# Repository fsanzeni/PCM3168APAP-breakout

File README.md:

# PCM3168APAP Breakout Board

A breakout board for the Texas Instruments PCM3168APAP audio codec, featuring 6 analog inputs and 8 analog outputs with high-quality buffering and filtering circuitry.
| PCB Front | PCB Back |
|-----------|----------|
|  |  |

## Overview

This evaluation board is based on the [TI TIDA-00609](https://www.ti.com/tool/TIDA-00609) reference design and provides a complete interface to the [PCM3168APAP](https://www.ti.com/product/PCM3168A/part-details/PCM3168APAP) - a 24-bit, 96kHz/192kHz, 6-in/8-out audio codec. The board includes analog input buffering with anti-aliasing filters, differential-to-single-ended output conversion, and integrated power regulation (via LDOs for 5v and 3.3v).

## Features

### Audio Codec
- **ADC**: 6-channel, 24-bit delta-sigma ADC with 107 dB dynamic range (differential), 104 dB (single-ended)
- **DAC**: 8-channel, 24-bit delta-sigma DAC with 112 dB dynamic range and differential 8V peak-to-peak outputs
- Sampling rates: 8 kHz to 192 kHz (ADC up to 96 kHz, DAC up to 192 kHz)
- Supports I²S, left-justified, right-justified, DSP, and TDM audio formats

### Analog Signal Path

#### Inputs (6 channels)
- 3.5mm TRS jack connectors for each stereo input pair
- Buffer and anti-aliasing low-pass filter based on [OPA4134](https://www.ti.com/product/OPA4134)/[OPA2134](https://www.ti.com/product/OPA2134) op-amps
- Configured for 2V RMS input, 0.5x gain, -3dB at 48 kHz 
- Output: 1V RMS to ADC
- Common-mode reference voltage (VCOMAD) generation

#### Outputs (8 channels)
- Two 6-pin headers providing 4 channels each
- Post-LPF and differential-to-single-ended conversion using OPA4134 op-amps
- Configured for 4V peak-to-peak DAC output, 0.747x gain, -3dB at 53 kHz
- Output: 2V RMS single-ended

### Digital Interface
- **I²S/Audio** (6-pin header): MCLK, BCK_ADC, LRCK_ADC, BCK_DAC, LRCK_DAC, and ground
- **I²C** (4-pin header): SDA, SCL, 3.3V, and ground
- **Digital Input** (4-pin header): DIN2, DIN3, SDIN (DIN1), and ground
- **Digital Output** (4-pin header): DOUT1, DOUT2, DOUT3, and ground
- **Reset** (2-pin header): Active-low reset with buffer IC ([SN74LVC2G34](https://www.ti.com/product/SN74LVC2G34))

### Configuration
- I²C mode (MODE pin tied to GND)
- I²C device address: 0x88
- Test points for ZERO and OVERFLOW flags
- Status LEDs: Green (ZERO), Yellow (OVERFLOW)

### Power Supply
- Input voltage: 6.2V to 18V
- Dual linear regulators (AMS1117):
  - 5V output for analog circuitry
  - 3.3V output for digital logic
- Comprehensive decoupling throughout

## BOM Highlights

### Key Components
- **IC101**: PCM3168APAP (HTQFP-64 package)
- **IC102**: SN74LVC2G34DRLR (dual buffer for reset/LEDs)
- **U201-U202, U301-U302**: OPA4134UA/OPA2134 (audio op-amps)
- **U401-U402**: AMS1117-5.0 and AMS1117-3.3 (linear regulators)

### Connectors
- J101: 6-pin I²S header
- J102: 4-pin I²C header
- J103-J104: 4-pin DIN/DOUT headers
- J201-J203: 3.5mm TRS analog input jacks
- J301-J302: 6-pin analog output headers
- J401: 2-pin power input

## Usage Notes

- Ensure proper power supply voltage range (6.2V minimum to avoid dropout on regulators) 
- The board is configured for I²C control by default
- All analog inputs accept balanced TRS connections or can be used with unbalanced sources
- Output headers provide differential pairs that have been converted to single-ended signals 

## License

[MIT License](./LICENSE)

## Revision History

- **v0.1** (2026-01-13): Initial release

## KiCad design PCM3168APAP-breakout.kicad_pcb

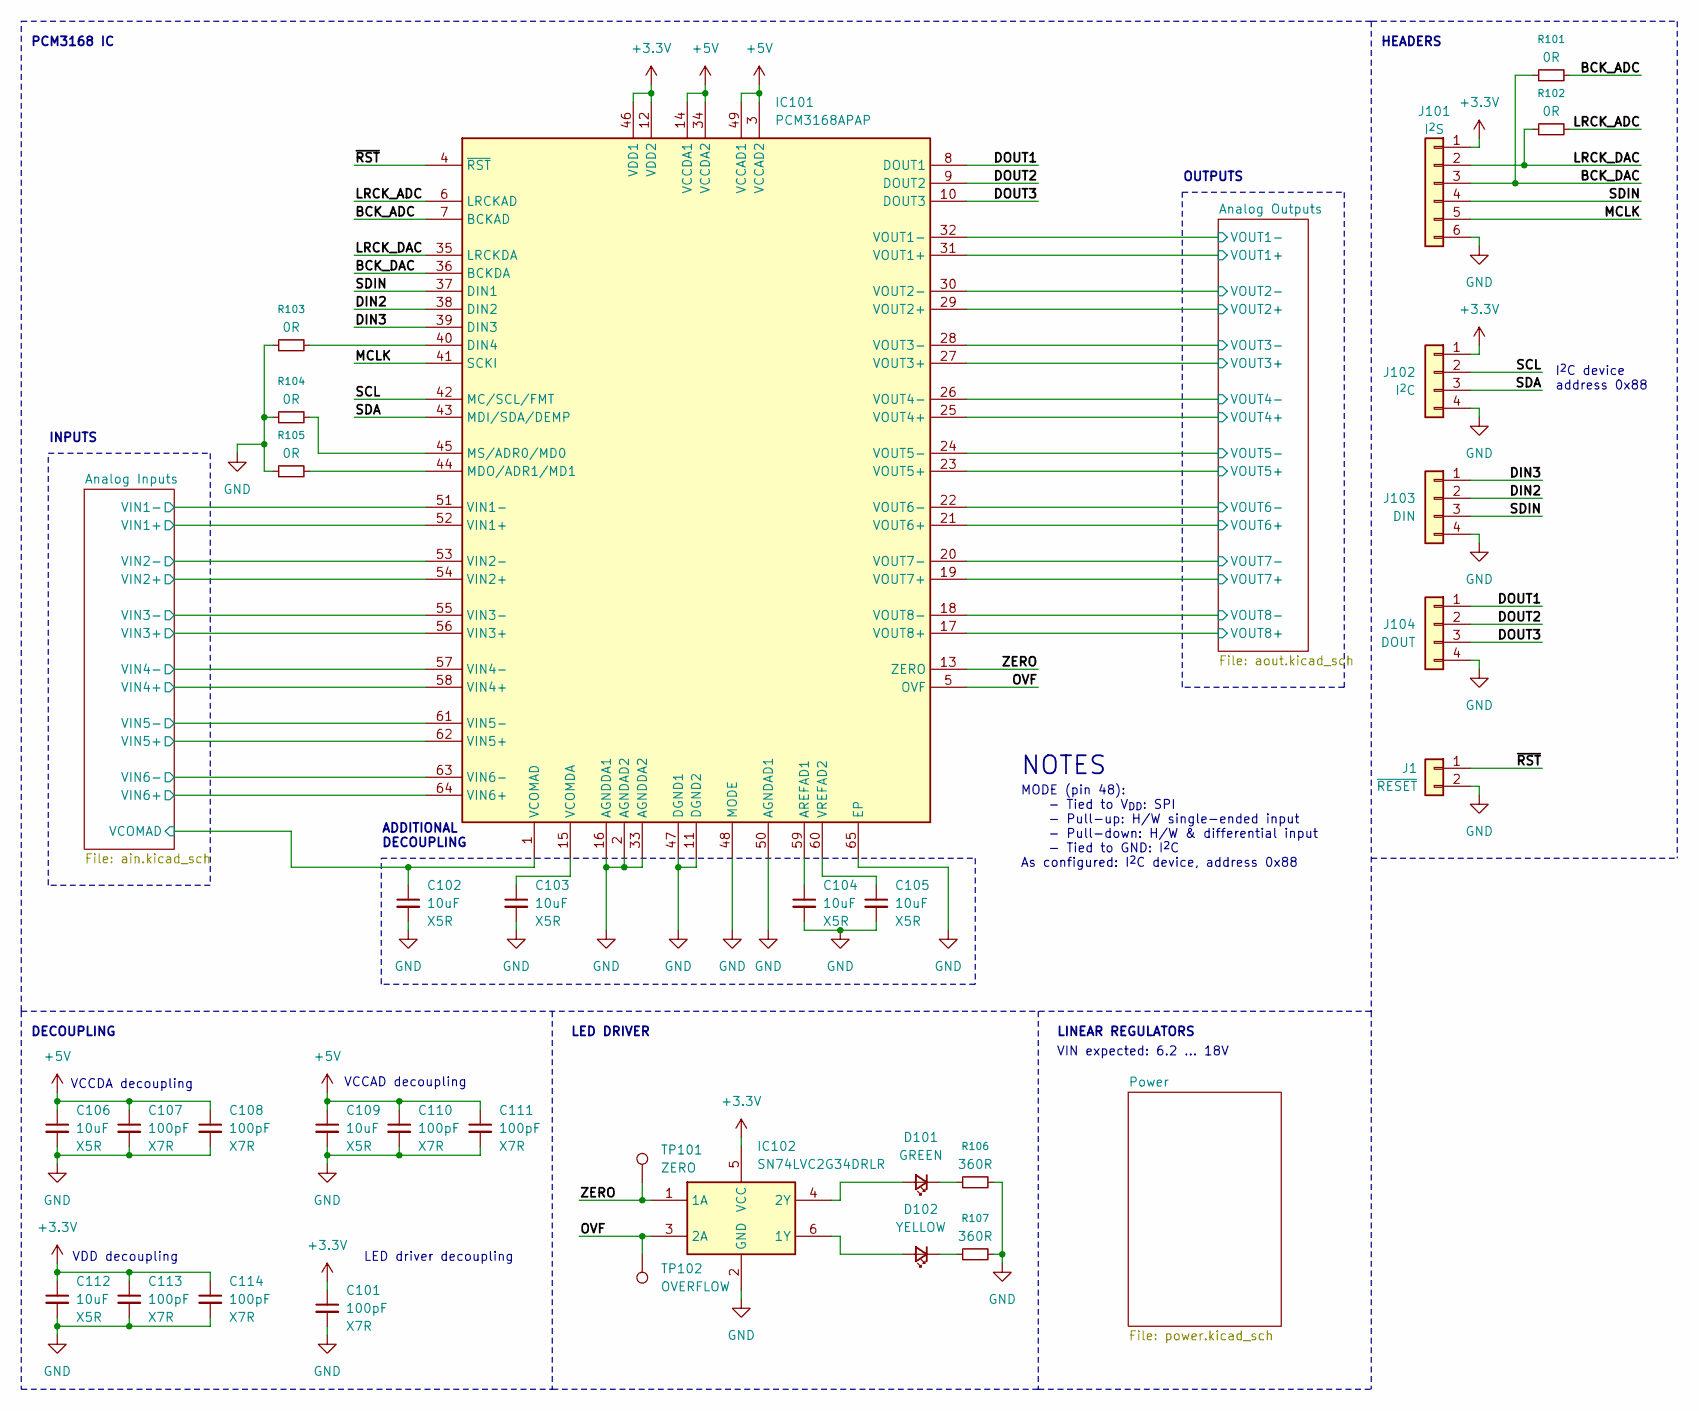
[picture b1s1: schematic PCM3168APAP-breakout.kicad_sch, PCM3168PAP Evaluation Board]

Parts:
C101, C107, C108, C110, C111, C113, C114: 100pF; C_0402_1005Metric
C102, C103, C104, C105, C106, C109, C112: 10uF; C_0603_1608Metric
D101: GREEN; LED_0603_1608Metric
D102: YELLOW; LED_0603_1608Metric
IC101: PCM3168APAP; QFP50P1200X1200X120-65N; Mouser Part Number 595-PCM3168APAP
IC102: SN74LVC2G34DRLR; SOTFL50P160X60-6N; Mouser Part Number 595-SN74LVC2G34DRLR
J1: ~{RESET}; PinHeader_1x02_P2.54mm_Vertical
J101: I^{2}S; PinHeader_1x06_P2.54mm_Vertical
J102: I^{2}C; PinHeader_1x04_P2.54mm_Vertical
J103: DIN; PinHeader_1x04_P2.54mm_Vertical
J104: DOUT; PinHeader_1x04_P2.54mm_Vertical
R101, R102, R103, R104, R105: 0R; R_0402_1005Metric
R106, R107: 360R; R_0402_1005Metric
TP101: ZERO; TestPoint_Pad_1.0x1.0mm
TP102: OVERFLOW; TestPoint_Pad_1.0x1.0mm

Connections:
+3.3V: C101.1, C112.1, C113.1, C114.1, IC101.12 (VDD2), IC101.46 (VDD1), IC102.5 (VCC), J101.1, J102.1; also elsewhere on the board
+5V: C106.1, C107.1, C108.1, C109.1, C110.1, C111.1, IC101.3 (VCCAD2), IC101.14 (VCCDA1), IC101.34 (VCCDA2), IC101.49 (VCCAD1); also elsewhere on the board
/Analog Inputs/VCOMAD: C102.1, IC101.1 (VCOMAD); also elsewhere on the board
/Analog Inputs/VIN1+: IC101.52 (VIN1+); also elsewhere on the board
/Analog Inputs/VIN1-: IC101.51 (VIN1-); also elsewhere on the board
/Analog Inputs/VIN2+: IC101.54 (VIN2+); also elsewhere on the board
/Analog Inputs/VIN2-: IC101.53 (VIN2-); also elsewhere on the board
/Analog Inputs/VIN3+: IC101.56 (VIN3+); also elsewhere on the board
/Analog Inputs/VIN3-: IC101.55 (VIN3-); also elsewhere on the board
/Analog Inputs/VIN4+: IC101.58 (VIN4+); also elsewhere on the board
/Analog Inputs/VIN4-: IC101.57 (VIN4-); also elsewhere on the board
/Analog Inputs/VIN5+: IC101.62 (VIN5+); also elsewhere on the board
/Analog Inputs/VIN5-: IC101.61 (VIN5-); also elsewhere on the board
/Analog Inputs/VIN6+: IC101.64 (VIN6+); also elsewhere on the board
/Analog Inputs/VIN6-: IC101.63 (VIN6-); also elsewhere on the board
/Analog Outputs/VOUT1+: IC101.31 (VOUT1+); also elsewhere on the board
/Analog Outputs/VOUT1-: IC101.32 (VOUT1-); also elsewhere on the board
/Analog Outputs/VOUT2+: IC101.29 (VOUT2+); also elsewhere on the board
/Analog Outputs/VOUT2-: IC101.30 (VOUT2-); also elsewhere on the board
/Analog Outputs/VOUT3+: IC101.27 (VOUT3+); also elsewhere on the board
/Analog Outputs/VOUT3-: IC101.28 (VOUT3-); also elsewhere on the board
/Analog Outputs/VOUT4+: IC101.25 (VOUT4+); also elsewhere on the board
/Analog Outputs/VOUT4-: IC101.26 (VOUT4-); also elsewhere on the board
/Analog Outputs/VOUT5+: IC101.23 (VOUT5+); also elsewhere on the board
/Analog Outputs/VOUT5-: IC101.24 (VOUT5-); also elsewhere on the board
/Analog Outputs/VOUT6+: IC101.21 (VOUT6+); also elsewhere on the board
/Analog Outputs/VOUT6-: IC101.22 (VOUT6-); also elsewhere on the board
/Analog Outputs/VOUT7+: IC101.19 (VOUT7+); also elsewhere on the board
/Analog Outputs/VOUT7-: IC101.20 (VOUT7-); also elsewhere on the board
/Analog Outputs/VOUT8+: IC101.17 (VOUT8+); also elsewhere on the board
/Analog Outputs/VOUT8-: IC101.18 (VOUT8-); also elsewhere on the board
/BCK_ADC: IC101.7 (BCKAD), R101.2
/BCK_DAC: IC101.36 (BCKDA), J101.3, R101.1
/DIN2: IC101.38 (DIN2), J103.2
/DIN3: IC101.39 (DIN3), J103.1
/DOUT1: IC101.8 (DOUT1), J104.1
/DOUT2: IC101.9 (DOUT2), J104.2
/DOUT3: IC101.10 (DOUT3), J104.3
/LRCK_ADC: IC101.6 (LRCKAD), R102.2
/LRCK_DAC: IC101.35 (LRCKDA), J101.2, R102.1
/MCLK: IC101.41 (SCKI), J101.5
/OVF: IC101.5 (OVF), IC102.3 (2A), TP102.1
/SCL: IC101.42 (MC/SCL/FMT), J102.2
/SDA: IC101.43 (MDI/SDA/DEMP), J102.3
/SDIN: IC101.37 (DIN1), J101.4, J103.3
/ZERO: IC101.13 (ZERO), IC102.1 (1A), TP101.1
/~RST: IC101.4 (~RST), J1.1
GND: C101.2, C102.2, C103.2, C104.2, C105.2, C106.2, C107.2, C108.2, C109.2, C110.2, C111.2, C112.2, C113.2, C114.2, IC101.2 (AGNDAD2), IC101.11 (DGND2), IC101.16 (AGNDDA1), IC101.33 (AGNDDA2), IC101.47 (DGND1), IC101.48 (MODE), IC101.50 (AGNDAD1), IC101.65 (EP), IC102.2 (GND), J1.2, J101.6, J102.4, J103.4, J104.4, R103.1, R104.1, R105.1, R106.2, R107.2; also elsewhere on the board
unnamed: D101.2 (A), IC102.4 (2Y)
unnamed: D101.1 (K), R106.1
unnamed: D102.2 (A), IC102.6 (1Y)
unnamed: D102.1 (K), R107.1
unnamed: C104.1, IC101.59 (AREFAD1)
unnamed: IC101.40 (DIN4), R103.2
unnamed: IC101.44 (MDO/ADR1/MD1), R105.2
unnamed: IC101.45 (MS/ADR0/MD0), R104.2
unnamed: C103.1, IC101.15 (VCOMDA)
unnamed: C105.1, IC101.60 (VREFAD2)

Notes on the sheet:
LED DRIVER
I^{2}C device address 0x88
DECOUPLING
PCM3168 IC
VCCAD decoupling
ADDITIONAL DECOUPLING
OUTPUTS
VDD decoupling
VCCDA decoupling
VIN expected: 6.2 ... 18V
LED driver decoupling
INPUTS
MODE (pin 48): - Tied to V_{DD}: SPI - Pull-up: H/W single-ended input - Pull-down: H/W & differential input - Tied to GND: I^{2}C As configured: I^{2}C device, address 0x88
NOTES
HEADERS
LINEAR REGULATORS

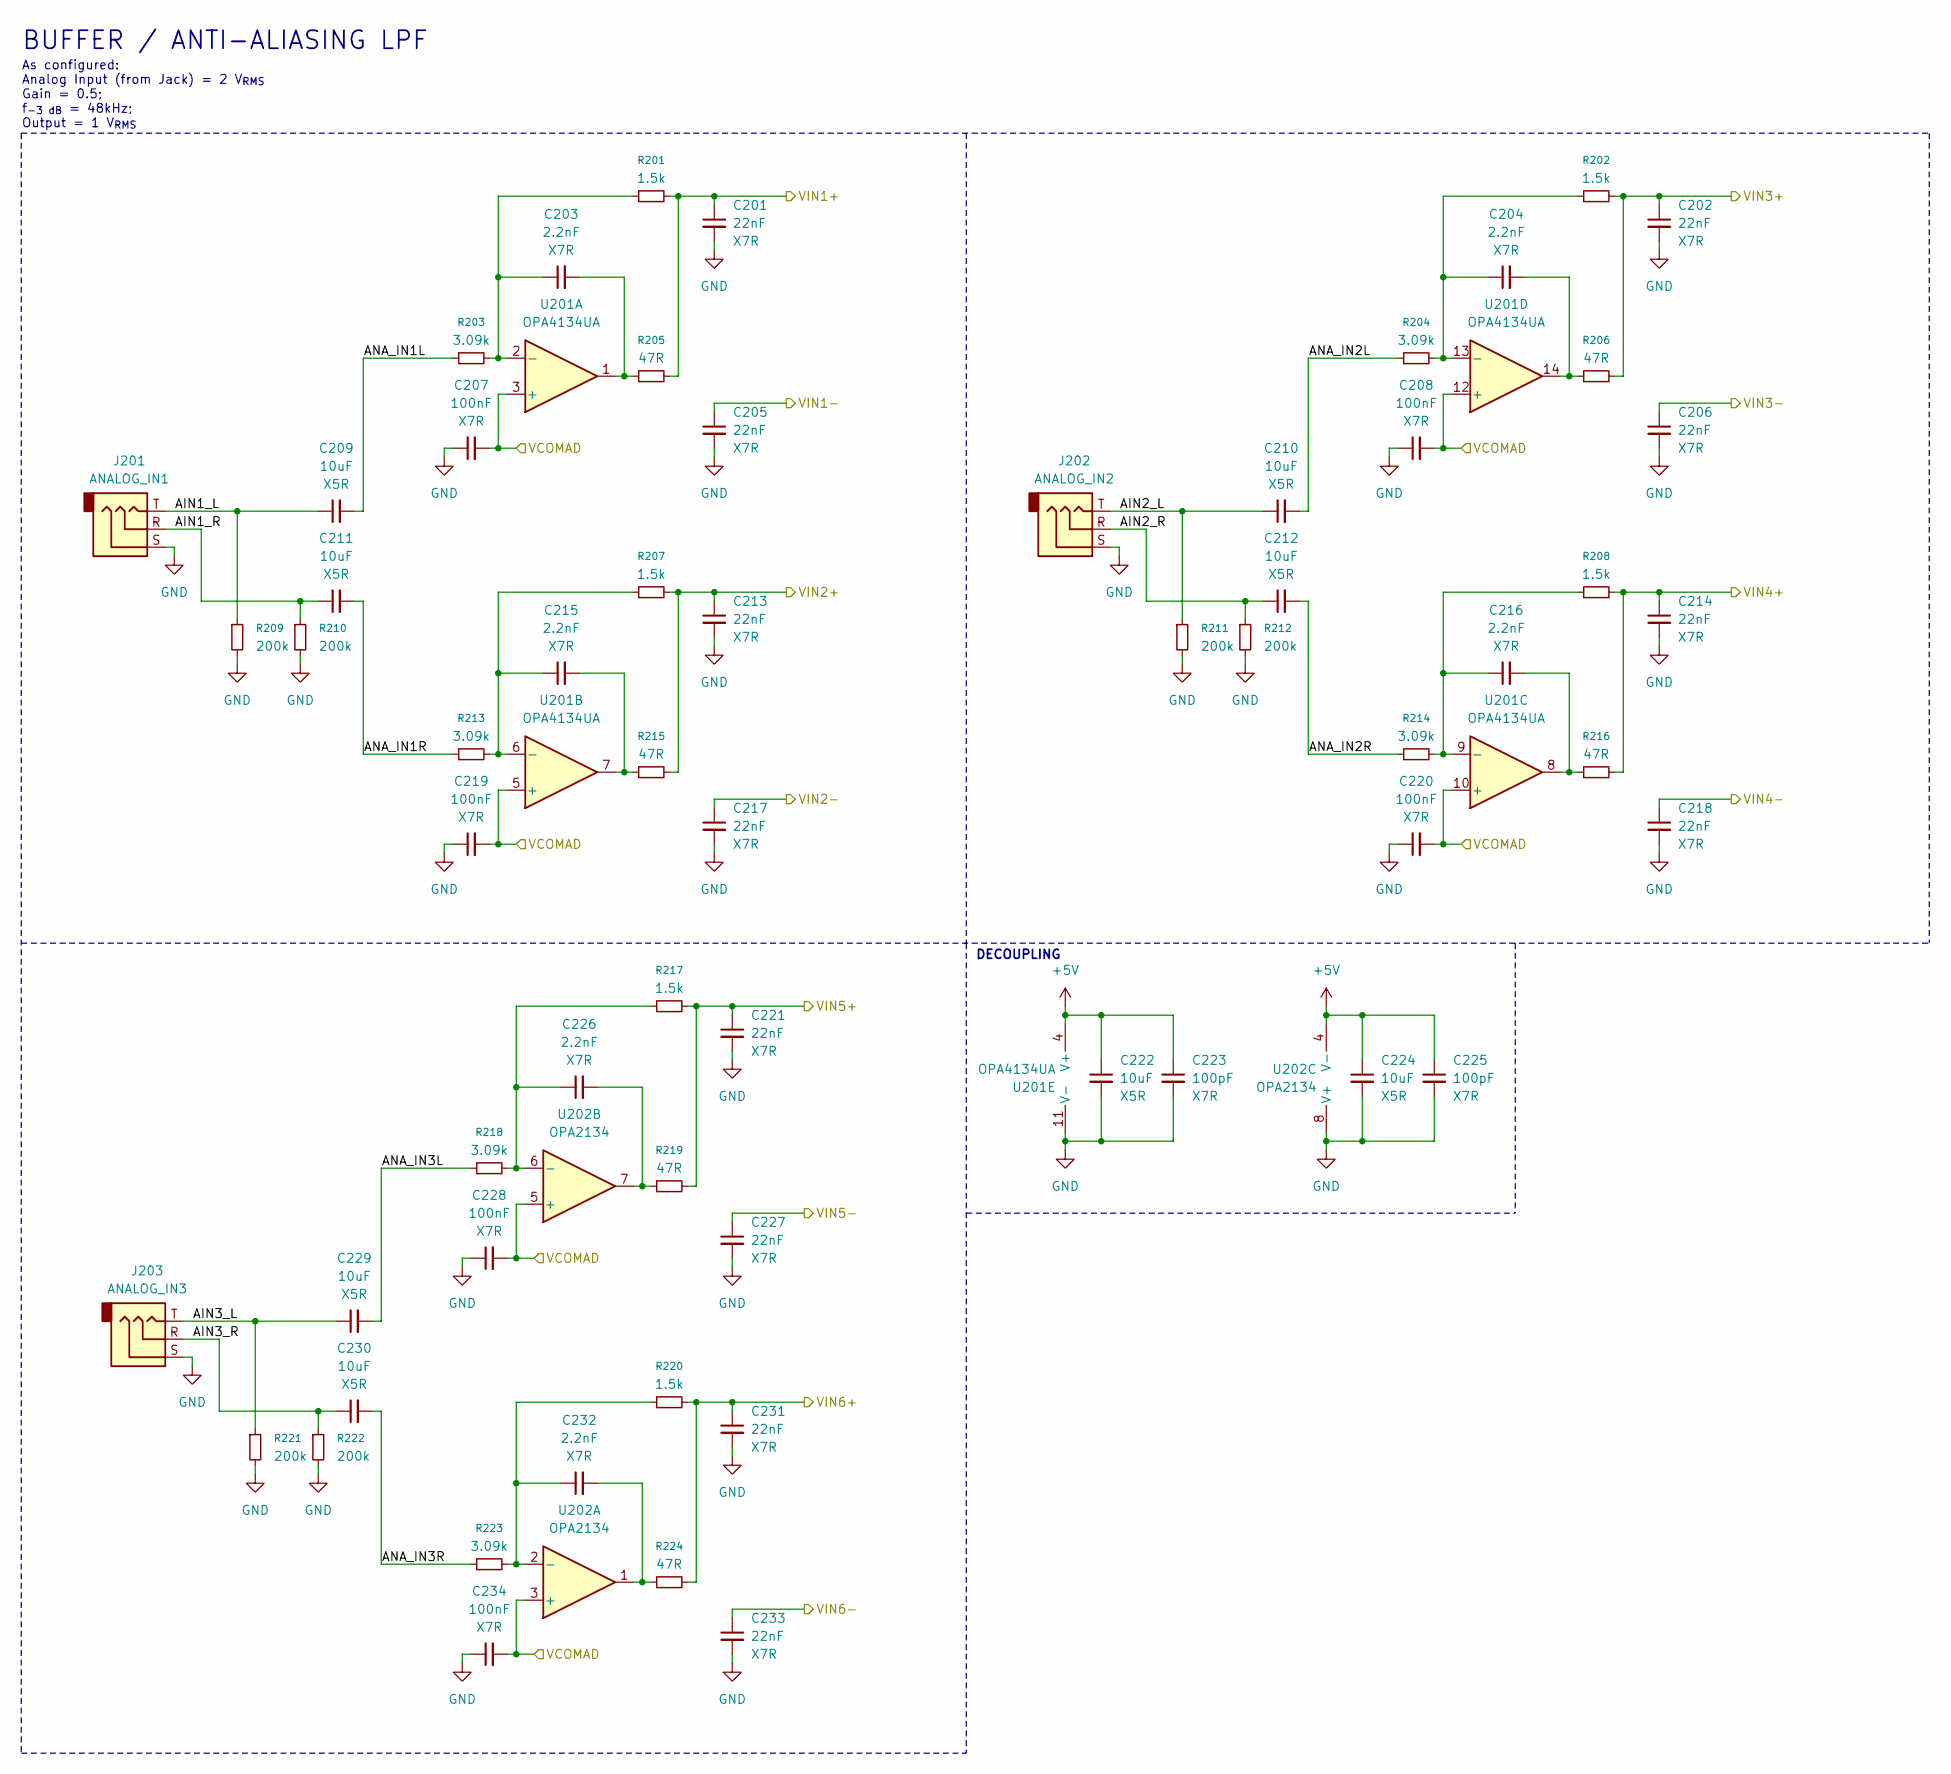
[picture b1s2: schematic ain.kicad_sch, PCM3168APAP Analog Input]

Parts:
C201, C202, C205, C206, C213, C214, C217, C218, C221, C227, C231, C233: 22nF; C_0402_1005Metric
C203, C204, C215, C216, C226, C232: 2.2nF; C_0402_1005Metric
C207, C208, C219, C220, C228, C234: 100nF; C_0402_1005Metric
C209, C210, C211, C212, C222, C224, C229, C230: 10uF; C_0603_1608Metric
C223, C225: 100pF; C_0402_1005Metric
J201: ANALOG_IN1; SJ335083ATR
J202: ANALOG_IN2; SJ335083ATR
J203: ANALOG_IN3; SJ335083ATR
R201, R202, R207, R208, R217, R220: 1.5k; R_0402_1005Metric
R203, R204, R213, R214, R218, R223: 3.09k; R_0402_1005Metric
R205, R206, R215, R216, R219, R224: 47R; R_0402_1005Metric
R209, R210, R211, R212, R221, R222: 200k; R_0402_1005Metric
U201: OPA4134UA; SOIC-14_3.9x8.7mm_P1.27mm
U202: OPA2134; SOIC-8_3.9x4.9mm_P1.27mm

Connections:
+5V: C222.1, C223.1, C224.1, C225.1, U201.4 (V+), U202.4 (V-); also elsewhere on the board
/Analog Inputs/AIN1_L: C209.1, J201.T, R209.1
/Analog Inputs/AIN1_R: C211.1, J201.R, R210.1
/Analog Inputs/AIN2_L: C210.1, J202.T, R211.1
/Analog Inputs/AIN2_R: C212.1, J202.R, R212.1
/Analog Inputs/AIN3_L: C229.1, J203.T, R221.1
/Analog Inputs/AIN3_R: C230.1, J203.R, R222.1
/Analog Inputs/ANA_IN1L: C209.2, R203.1
/Analog Inputs/ANA_IN1R: C211.2, R213.1
/Analog Inputs/ANA_IN2L: C210.2, R204.1
/Analog Inputs/ANA_IN2R: C212.2, R214.1
/Analog Inputs/ANA_IN3L: C229.2, R218.1
/Analog Inputs/ANA_IN3R: C230.2, R223.1
/Analog Inputs/VCOMAD: C207.2, C208.2, C219.2, C220.2, C228.2, C234.2, U201.3 (+), U201.5 (+), U201.10 (+), U201.12 (+), U202.3 (+), U202.5 (+); also elsewhere on the board
/Analog Inputs/VIN1+: C201.1, R201.2, R205.2; also elsewhere on the board
/Analog Inputs/VIN1-: C205.1; also elsewhere on the board
/Analog Inputs/VIN2+: C213.1, R207.2, R215.2; also elsewhere on the board
/Analog Inputs/VIN2-: C217.1; also elsewhere on the board
/Analog Inputs/VIN3+: C202.1, R202.2, R206.2; also elsewhere on the board
/Analog Inputs/VIN3-: C206.1; also elsewhere on the board
/Analog Inputs/VIN4+: C214.1, R208.2, R216.2; also elsewhere on the board
/Analog Inputs/VIN4-: C218.1; also elsewhere on the board
/Analog Inputs/VIN5+: C221.1, R217.2, R219.2; also elsewhere on the board
/Analog Inputs/VIN5-: C227.1; also elsewhere on the board
/Analog Inputs/VIN6+: C231.1, R220.2, R224.2; also elsewhere on the board
/Analog Inputs/VIN6-: C233.1; also elsewhere on the board
GND: C201.2, C202.2, C205.2, C206.2, C207.1, C208.1, C213.2, C214.2, C217.2, C218.2, C219.1, C220.1, C221.2, C222.2, C223.2, C224.2, C225.2, C227.2, C228.1, C231.2, C233.2, C234.1, J201.S, J202.S, J203.S, R209.2, R210.2, R211.2, R212.2, R221.2, R222.2, U201.11 (V-), U202.8 (V+); also elsewhere on the board
unnamed: C203.2, R205.1, U201.1
unnamed: C204.2, R206.1, U201.14
unnamed: C215.2, R215.1, U201.7
unnamed: C216.2, R216.1, U201.8
unnamed: C226.2, R219.1, U202.7
unnamed: C232.2, R224.1, U202.1
unnamed: C203.1, R201.1, R203.2, U201.2 (-)
unnamed: C215.1, R207.1, R213.2, U201.6 (-)
unnamed: C216.1, R208.1, R214.2, U201.9 (-)
unnamed: C204.1, R202.1, R204.2, U201.13 (-)
unnamed: C232.1, R220.1, R223.2, U202.2 (-)
unnamed: C226.1, R217.1, R218.2, U202.6 (-)

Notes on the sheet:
DECOUPLING
BUFFER / ANTI-ALIASING LPF
As configured: Analog Input (from Jack) = 2 V_{RMS} Gain = 0.5; f_{-3 dB} = 48kHz; Output = 1 V_{RMS}

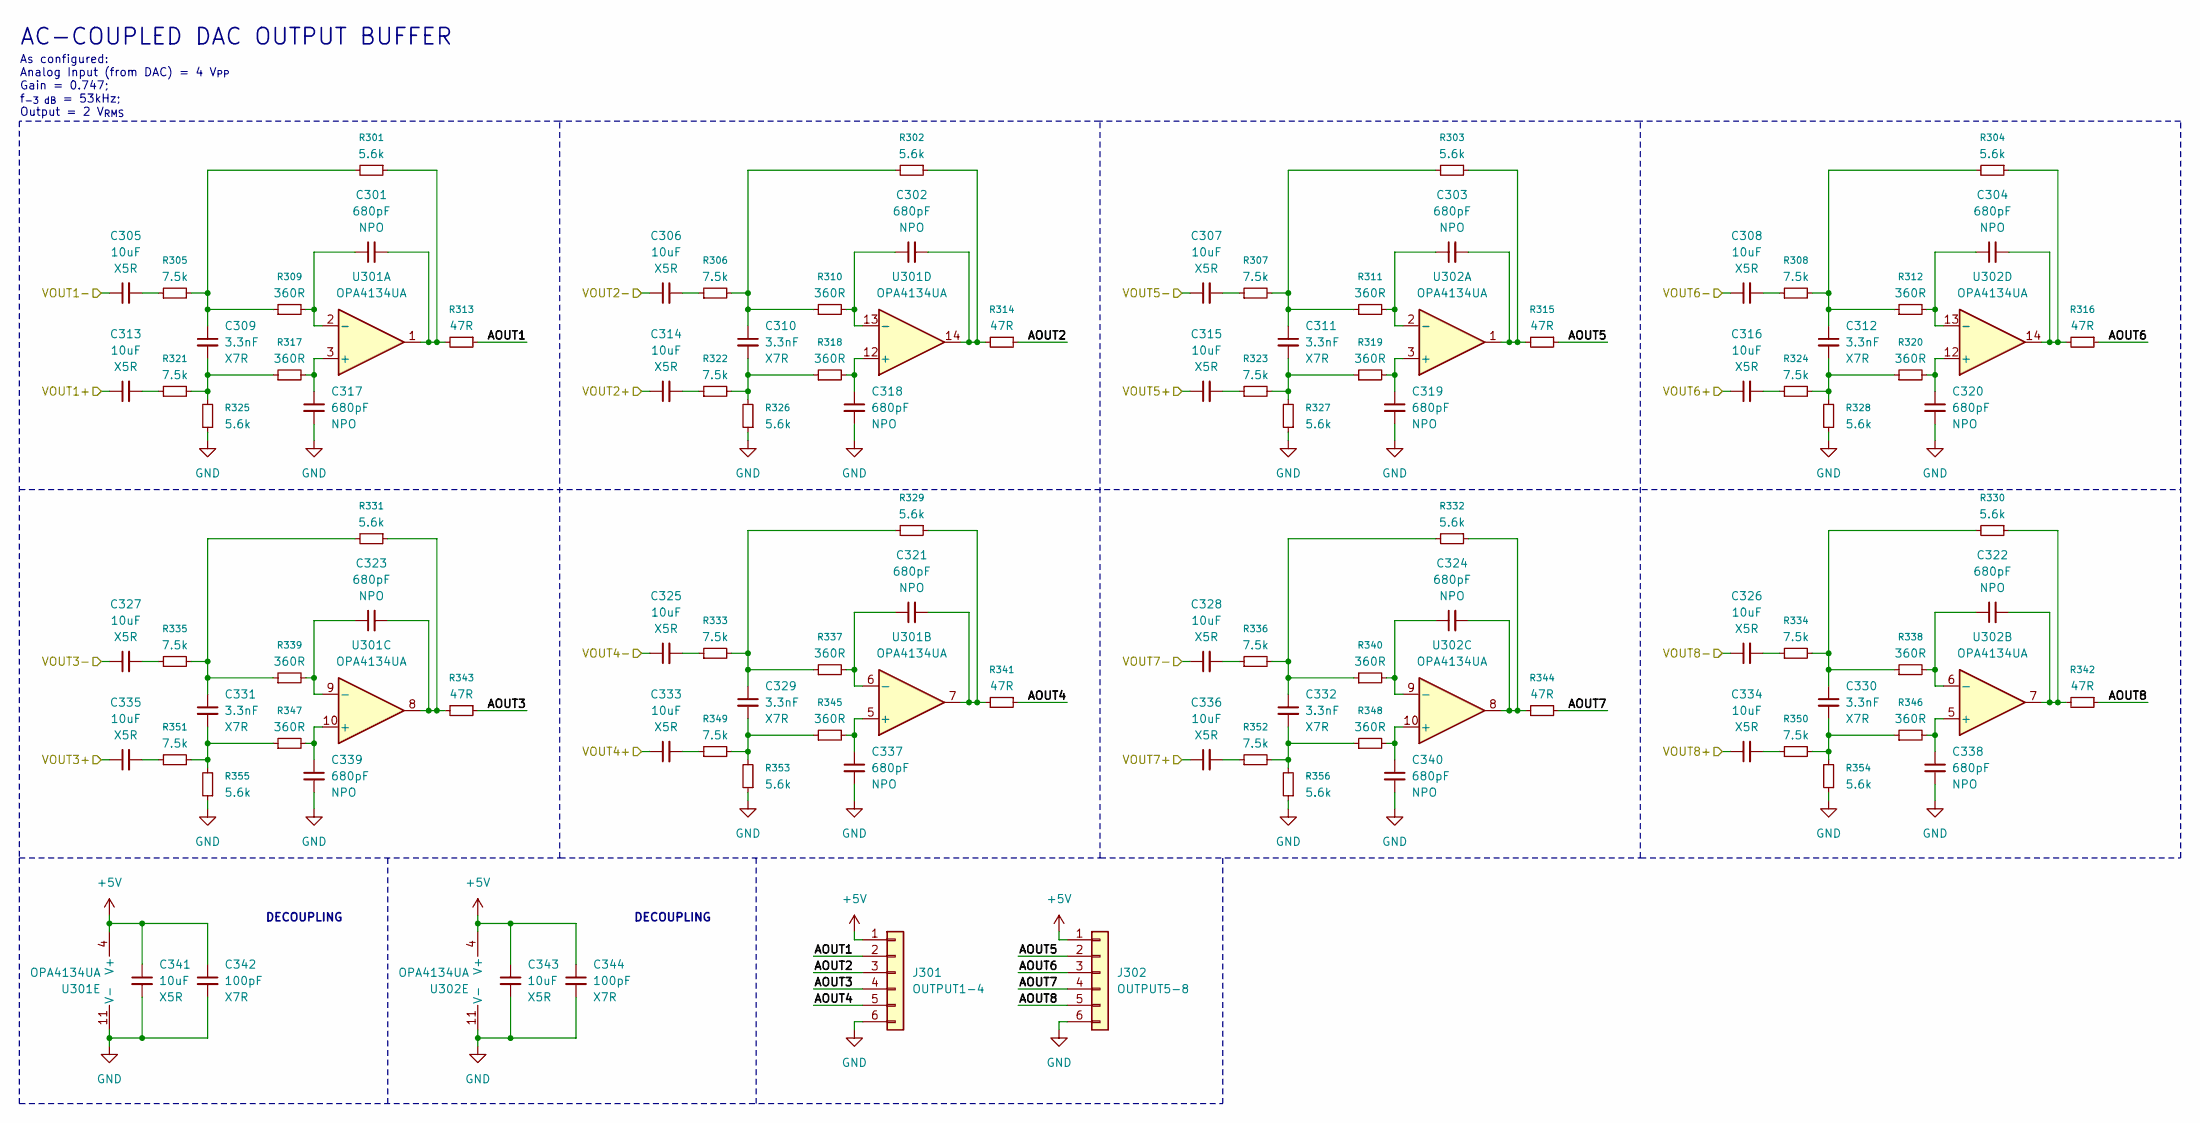
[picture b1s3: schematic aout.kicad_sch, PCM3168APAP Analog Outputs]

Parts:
C301, C302, C303, C304, C321, C322, C323, C324: 680pF; C_0603_1608Metric
C305, C306, C307, C308, C313, C314, C315, C316, C325, C326, C327, C328, C333, C334, C335, C336, C341, C343: 10uF; C_0603_1608Metric
C309, C310, C311, C312, C329, C330, C331, C332: 3.3nF; C_0402_1005Metric
C317, C318, C319, C320, C337, C338, C339, C340: 680pF; C_0402_1005Metric
C342, C344: 100pF; C_0402_1005Metric
J301: OUTPUT1-4; PinHeader_1x06_P2.54mm_Vertical
J302: OUTPUT5-8; PinHeader_1x06_P2.54mm_Vertical
R301, R302, R303, R304, R325, R326, R327, R328, R329, R330, R331, R332, R353, R354, R355, R356: 5.6k; R_0402_1005Metric
R305, R306, R307, R308, R321, R322, R323, R324, R333, R334, R335, R336, R349, R350, R351, R352: 7.5k; R_0402_1005Metric
R309, R310, R311, R312, R317, R318, R319, R320, R337, R338, R339, R340, R345, R346, R347, R348: 360R; R_0402_1005Metric
R313, R314, R315, R316, R341, R342, R343, R344: 47R; R_0402_1005Metric
U301, U302: OPA4134UA; SOIC-14_3.9x8.7mm_P1.27mm

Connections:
+5V: C341.1, C342.1, C343.1, C344.1, J301.1, J302.1, U301.4 (V+), U302.4 (V+); also elsewhere on the board
/Analog Outputs/AOUT1: J301.2, R313.1
/Analog Outputs/AOUT2: J301.3, R314.1
/Analog Outputs/AOUT3: J301.4, R343.1
/Analog Outputs/AOUT4: J301.5, R341.1
/Analog Outputs/AOUT5: J302.2, R315.1
/Analog Outputs/AOUT6: J302.3, R316.1
/Analog Outputs/AOUT7: J302.4, R344.1
/Analog Outputs/AOUT8: J302.5, R342.1
/Analog Outputs/VOUT1+: C313.1; also elsewhere on the board
/Analog Outputs/VOUT1-: C305.1; also elsewhere on the board
/Analog Outputs/VOUT2+: C314.1; also elsewhere on the board
/Analog Outputs/VOUT2-: C306.1; also elsewhere on the board
/Analog Outputs/VOUT3+: C335.1; also elsewhere on the board
/Analog Outputs/VOUT3-: C327.1; also elsewhere on the board
/Analog Outputs/VOUT4+: C333.1; also elsewhere on the board
/Analog Outputs/VOUT4-: C325.1; also elsewhere on the board
/Analog Outputs/VOUT5+: C315.1; also elsewhere on the board
/Analog Outputs/VOUT5-: C307.1; also elsewhere on the board
/Analog Outputs/VOUT6+: C316.1; also elsewhere on the board
/Analog Outputs/VOUT6-: C308.1; also elsewhere on the board
/Analog Outputs/VOUT7+: C336.1; also elsewhere on the board
/Analog Outputs/VOUT7-: C328.1; also elsewhere on the board
/Analog Outputs/VOUT8+: C334.1; also elsewhere on the board
/Analog Outputs/VOUT8-: C326.1; also elsewhere on the board
GND: C317.2, C318.2, C319.2, C320.2, C337.2, C338.2, C339.2, C340.2, C341.2, C342.2, C343.2, C344.2, J301.6, J302.6, R325.1, R326.1, R327.1, R328.1, R353.1, R354.1, R355.1, R356.1, U301.11 (V-), U302.11 (V-); also elsewhere on the board
unnamed: C301.2, R301.1, R313.2, U301.1
unnamed: C302.2, R302.1, R314.2, U301.14
unnamed: C303.2, R303.1, R315.2, U302.1
unnamed: C304.2, R304.1, R316.2, U302.14
unnamed: C305.2, R305.1
unnamed: C306.2, R306.1
unnamed: C307.2, R307.1
unnamed: C308.2, R308.1
unnamed: C309.1, R301.2, R305.2, R309.1
unnamed: C309.2, R317.1, R321.2, R325.2
unnamed: C310.1, R302.2, R306.2, R310.1
unnamed: C310.2, R318.1, R322.2, R326.2
unnamed: C311.1, R303.2, R307.2, R311.1
unnamed: C311.2, R319.1, R323.2, R327.2
unnamed: C312.1, R304.2, R308.2, R312.1
unnamed: C312.2, R320.1, R324.2, R328.2
unnamed: C313.2, R321.1
unnamed: C314.2, R322.1
unnamed: C315.2, R323.1
unnamed: C316.2, R324.1
unnamed: C321.2, R329.1, R341.2, U301.7
unnamed: C322.2, R330.1, R342.2, U302.7
unnamed: C323.2, R331.1, R343.2, U301.8
unnamed: C324.2, R332.1, R344.2, U302.8
unnamed: C325.2, R333.1
unnamed: C326.2, R334.1
unnamed: C327.2, R335.1
unnamed: C328.2, R336.1
unnamed: C329.1, R329.2, R333.2, R337.1
unnamed: C329.2, R345.1, R349.2, R353.2
unnamed: C330.1, R330.2, R334.2, R338.1
unnamed: C330.2, R346.1, R350.2, R354.2
unnamed: C331.1, R331.2, R335.2, R339.1
unnamed: C331.2, R347.1, R351.2, R355.2
unnamed: C332.1, R332.2, R336.2, R340.1
unnamed: C332.2, R348.1, R352.2, R356.2
unnamed: C333.2, R349.1
unnamed: C334.2, R350.1
unnamed: C335.2, R351.1
unnamed: C336.2, R352.1
unnamed: C317.1, R317.2, U301.3 (+)
unnamed: C301.1, R309.2, U301.2 (-)
unnamed: C337.1, R345.2, U301.5 (+)
unnamed: C321.1, R337.2, U301.6 (-)
unnamed: C339.1, R347.2, U301.10 (+)
unnamed: C323.1, R339.2, U301.9 (-)
unnamed: C318.1, R318.2, U301.12 (+)
unnamed: C302.1, R310.2, U301.13 (-)
unnamed: C319.1, R319.2, U302.3 (+)
unnamed: C303.1, R311.2, U302.2 (-)
unnamed: C338.1, R346.2, U302.5 (+)
unnamed: C322.1, R338.2, U302.6 (-)
unnamed: C340.1, R348.2, U302.10 (+)
unnamed: C324.1, R340.2, U302.9 (-)
unnamed: C320.1, R320.2, U302.12 (+)
unnamed: C304.1, R312.2, U302.13 (-)

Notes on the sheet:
As configured: Analog Input (from DAC) = 4 V_{PP} Gain = 0.747; f_{-3 dB} = 53kHz; Output = 2 V_{RMS}
DECOUPLING
AC-COUPLED DAC OUTPUT BUFFER

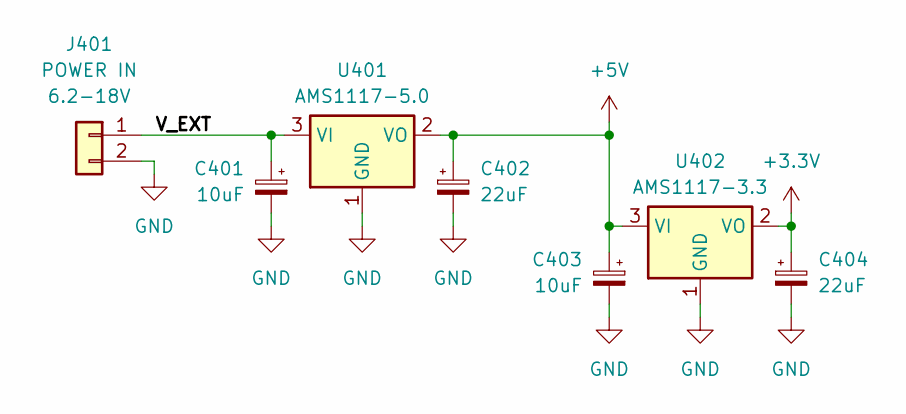
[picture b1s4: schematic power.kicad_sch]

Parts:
C401, C403: 10uF; CP_Elec_5x5.3
C402, C404: 22uF; CP_Elec_5x5.3
J401: POWER IN; Samtec_HPM-02-01-x-S_Straight_1x02_Pitch5.08mm
U401: AMS1117-5.0; SOT-223-3_TabPin2
U402: AMS1117-3.3; SOT-223-3_TabPin2

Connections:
+3.3V: C404.1, U402.2 (VO); also elsewhere on the board
+5V: C402.1, C403.1, U401.2 (VO), U402.3 (VI); also elsewhere on the board
/Power/V_EXT: C401.1, J401.1, U401.3 (VI)
GND: C401.2, C402.2, C403.2, C404.2, J401.2, U401.1 (GND), U402.1 (GND); also elsewhere on the board

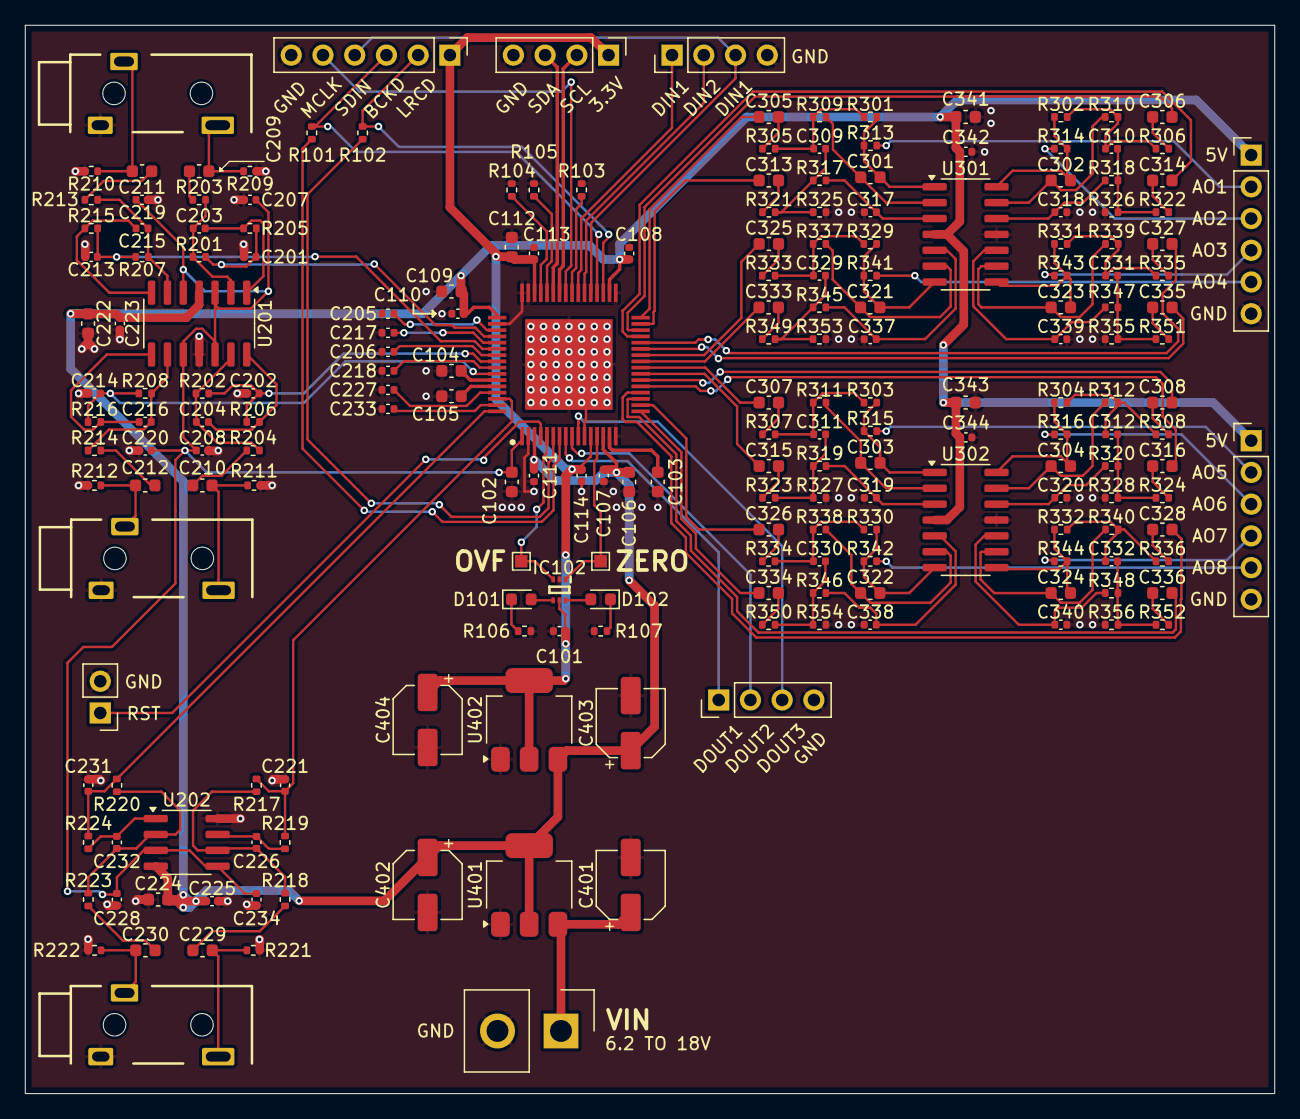
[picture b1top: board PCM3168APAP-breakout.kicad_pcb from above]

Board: 4 copper layers, 100.0 x 85.5 mm, 206 parts (0 on the bottom side), 147 nets.

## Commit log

2026-01-13 schematic finished
2026-01-13 schematic formatting
2026-01-13 added current schematic pdf
2026-01-14 Cleaned up schematic
2026-01-15 finished routin, updated schematic, added PDF
2026-01-15 finish routing, fix schematic, add images and PDF
2026-01-15 fix README
2026-01-15 add images to README
